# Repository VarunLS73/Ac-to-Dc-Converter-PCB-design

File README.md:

# Ac-to-Dc-Converter-PCB-design
An AC to DC converter is an essential circuit used in various electronic
applications to convert high-voltage alternating current (AC) into lowvoltage
direct current (DC). This project focuses on designing and implementing
an AC to DC converter that steps down 220V AC mains supply to
a stable 5V DC output.

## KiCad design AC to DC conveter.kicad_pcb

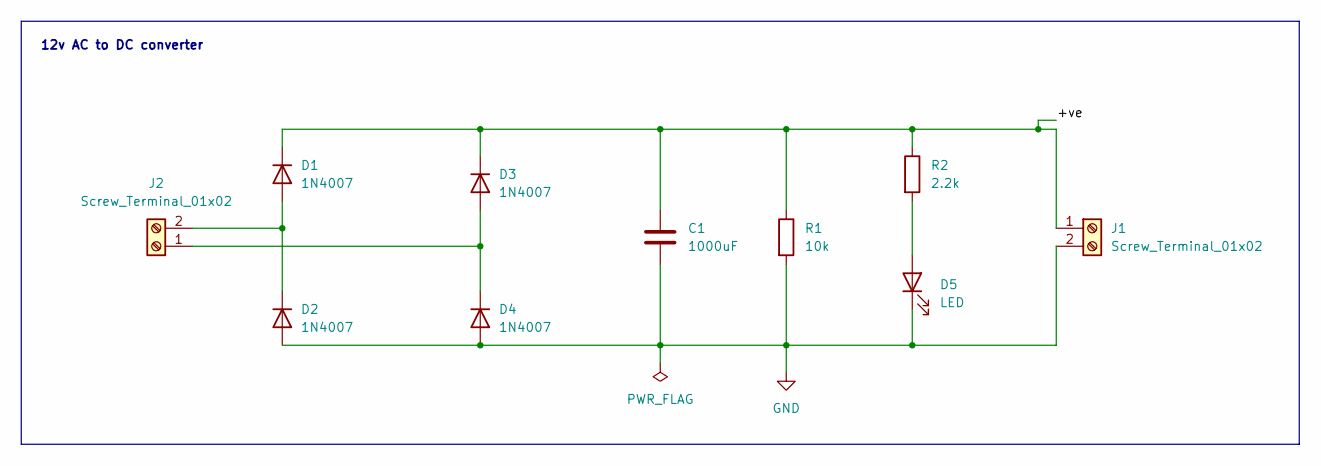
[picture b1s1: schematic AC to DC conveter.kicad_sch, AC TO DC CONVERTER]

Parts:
C1: 1000uF; CP_Radial_D13.0mm_P5.00mm
D1, D2, D3, D4: 1N4007; D_DO-41_SOD81_P10.16mm_Horizontal
D5: LED; LED_D5.0mm
J1, J2: Screw_Terminal_01x02; TerminalBlock_bornier-3_P5.08mm
R1: 10k; R_Axial_DIN0204_L3.6mm_D1.6mm_P5.08mm_Horizontal
R2: 2.2k; R_Axial_DIN0204_L3.6mm_D1.6mm_P5.08mm_Horizontal

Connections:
/+ve: C1.1, D1.1 (K), D3.1 (K), J1.1, R1.1, R2.1
GND: C1.2, D2.2 (A), D4.2 (A), D5.1 (K), J1.2, R1.2
unnamed: D1.2 (A), D2.1 (K), J2.2
unnamed: D3.2 (A), D4.1 (K), J2.1
unnamed: D5.2 (A), R2.2

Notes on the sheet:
12v AC to DC converter

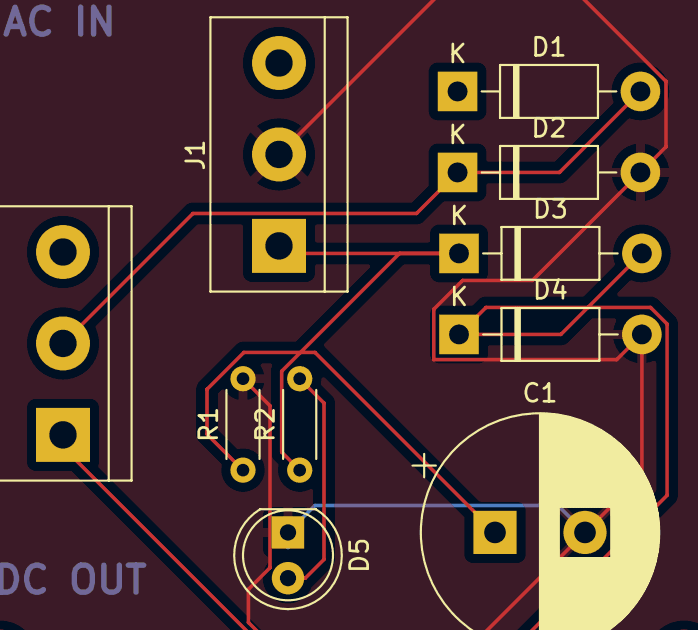
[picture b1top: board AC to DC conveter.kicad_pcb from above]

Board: 2 copper layers, 10 parts (0 on the bottom side), 5 nets.
